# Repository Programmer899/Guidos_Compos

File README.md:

# Guidos_Compos
### - What is this project
My idea for this project is a little by the time I had left, meaning that it could not be too complex.
Therefore I ended up choosing a compass because I were interested in knowing how the magnetometer works.

### - What purpose does it have
We all know that you do not want to get stuck somewhere with a map but lost the compass along the way.
Therefore I have made this simple compass that simply points to north.

In addition to be a helping hand when reading the map, it is a sort of project that gives you perspective and learn stuff along the way.
Some of this is done in educational purpose.

### - Description:
It is a simple compas using a MMC5983MA-Magnetometer to detirmine the direction of the earth's magnetic field.
To read the values my "Guidos Compos" is using a bare minimum "ATtiny45-20SU SO-8" as it's cpu.
As for the power source, I am inputing power from a 3.7V 500mAh battery that is beeing lowered down to 3.3V for the "ATtiny" and the "Magnetometer". The leds are then powered directly from the battery and beeing controlled by the Attiny.
At some places there are also some capacitors placed out to take in fact of the small noise in the power, which can be an outcome from the battery. What the meaning of the capacitor is to balance out the noice giving you: noise -> mostly clear.

### - Problems along the way:
I have had a few problems along the way, as an example the wiring. I had to redo the entire wiring after noticing that my led lights were rotated incorrectly.
I have also had a little to much going on during this PCB week on [Half Life](https://halflife.hackclub.com/) meaning that I have not had much time to work on my project.
Though, in the end I got something to hopefully work.
### - Firmware:
[Firmware - Built](https://github.com/Programmer899/Guidos_Compos/blob/main/firmware.hex)
---
## Schematic:

## PCB

## 3D View

### Build Of Materials
**#** | **Item**                 | **Qty** | **Supplier** | **Cost/item** | **Total Cost** | **link**                                                                                                                     
-------|--------------------------|---------|--------------|---------------|----------------|------------------------------------------------------------------------------------------------------------------------------
 **1** | Voltage Regulator 3\.3V  | 1       | Electrokit   | $0\.13        | $0\.13         | https://www\.electrokit\.com/en/l7833\-sot\-223\-voltage\-regulator\-3\.3v\-1a                                               
 **2** | Attiny45                 | 1       | Electrokit   | $2\.90        | $2\.90         | https://www\.electrokit\.com/en/attiny45\-20su\-so\-8\-8\-bit\-mcu\-flash\-4k                                                
 **3** | Battery charger          | 1       | Electrokit   | $5\.50        | $5\.50         | https://www\.electrokit\.com/en/tp4056\-batteriladdare\-lipo\-microusb                                                       
 **4** | SK6812\-E                | 25      | Amazon       | $0\.04        | $1\.00         | https://www\.amazon\.se/gp/product/B0GGJFR5QX/ref=sw\_img\_1?smid=A2WIE6SW95T3HY&psc=1                                       
 **5** | Battery                  | 1       | Conrad       | $8\.90        | $8\.90         | https://www\.conrad\.se/sv/p/amewi\-rc\-batteripack\-lipo\-3\-7\-v\-500\-mah\-antal\-celler\-1\-softcase\-jst\-3436344\.html 
 **6** | MMC5983MA                | 1       | Digikey      | $3\.32        | $3\.32         | https://www\.digikey\.com/en/products/detail/memsic\-inc/MMC5983MA/10452795                                                  
 **TOTAL** | Estimated total shipping |         |              |               | $8\.23         |
 
 **NOTE:**
 The shipping is not fully accurate due to me having insuffisient time for the project - Time = money.  
 Meaning that the **shipping** is for Electrokit and Amazon. Conrad and Digikey are outside the money-range.

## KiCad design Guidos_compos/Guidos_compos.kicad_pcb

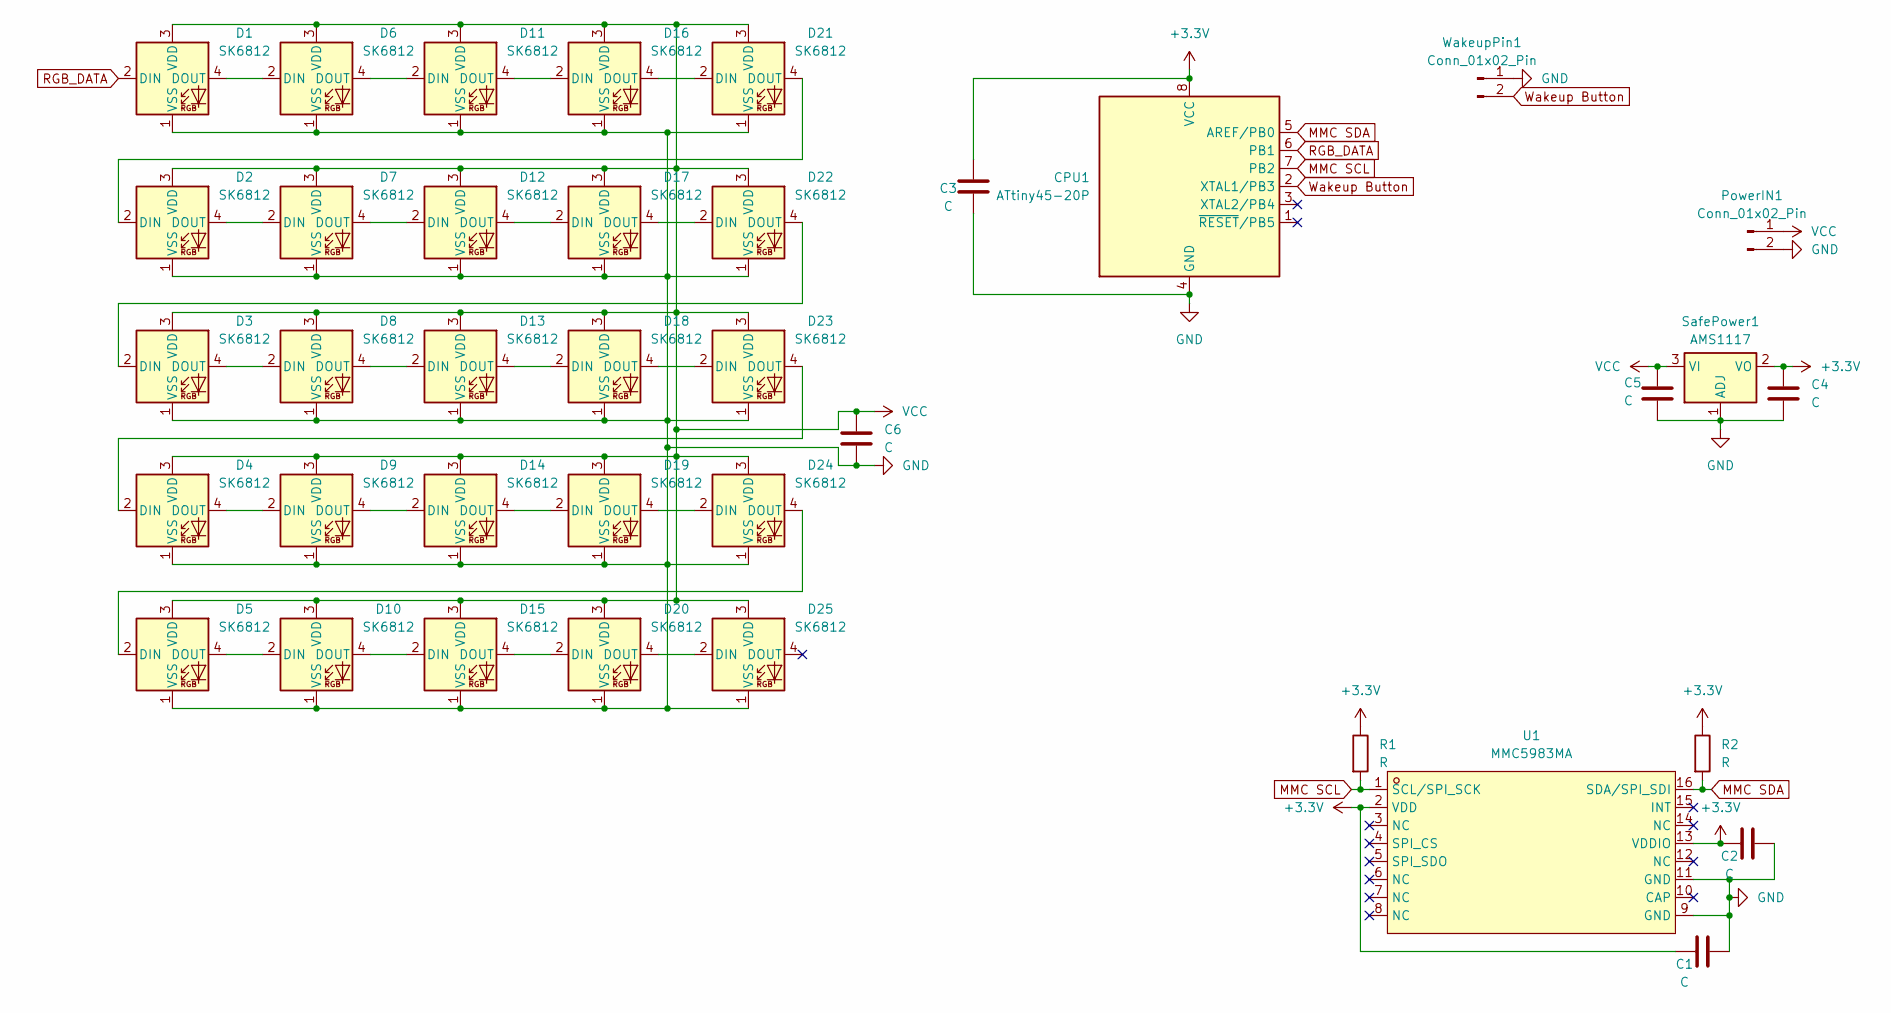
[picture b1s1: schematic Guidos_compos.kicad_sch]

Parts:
C1, C2, C3, C4, C5, C6: C; PinHeader_1x02_P1.00mm_Vertical
CPU1: ATtiny45-20P; DIP-8_W7.62mm
D1, D2, D3, D4, D5, D6, D7, D8, D9, D10, D11, D12, D13, D14, D15, D16, D17, D18, D19, D20, D21, D22, D23, D24, D25: SK6812; LED_SK6812_PLCC4_5.0x5.0mm_P3.2mm
PowerIN1: Conn_01x02_Pin; PinHeader_1x02_P1.00mm_Vertical
R1, R2: R; PinHeader_1x02_P1.00mm_Vertical
SafePower1: AMS1117; SOT-223-3_TabPin2
U1: MMC5983MA; MPN MMC5983MA; LCSC Part C404329
WakeupPin1: Conn_01x02_Pin; PinHeader_1x02_P1.00mm_Vertical

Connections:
+3.3V: C1.2, C2.2, C3.2, C4.1, CPU1.8 (VCC), R1.1, R2.1, SafePower1.2 (VO), U1.2 (VDD), U1.13 (VDDIO)
GND: C1.1, C2.1, C3.1, C4.2, C5.2, C6.2, CPU1.4 (GND), D1.1 (VSS), D2.1 (VSS), D3.1 (VSS), D4.1 (VSS), D5.1 (VSS), D6.1 (VSS), D7.1 (VSS), D8.1 (VSS), D9.1 (VSS), D10.1 (VSS), D11.1 (VSS), D12.1 (VSS), D13.1 (VSS), D14.1 (VSS), D15.1 (VSS), D16.1 (VSS), D17.1 (VSS), D18.1 (VSS), D19.1 (VSS), D20.1 (VSS), D21.1 (VSS), D22.1 (VSS), D23.1 (VSS), D24.1 (VSS), D25.1 (VSS), PowerIN1.2, SafePower1.1 (ADJ), U1.9 (GND), U1.11 (GND), WakeupPin1.1
MMC SCL: CPU1.7 (PB2), R1.2, U1.1 (SCL/SPI_SCK)
MMC SDA: CPU1.5 (AREF/PB0), R2.2, U1.16 (SDA/SPI_SDI)
unnamed: D1.4 (DOUT), D6.2 (DIN)
unnamed: D2.2 (DIN), D21.4 (DOUT)
unnamed: D2.4 (DOUT), D7.2 (DIN)
unnamed: D3.4 (DOUT), D8.2 (DIN)
unnamed: D4.4 (DOUT), D9.2 (DIN)
unnamed: D5.4 (DOUT), D10.2 (DIN)
unnamed: D10.4 (DOUT), D15.2 (DIN)
unnamed: D6.4 (DOUT), D11.2 (DIN)
unnamed: D11.4 (DOUT), D16.2 (DIN)
unnamed: D7.4 (DOUT), D12.2 (DIN)
unnamed: D12.4 (DOUT), D17.2 (DIN)
unnamed: D8.4 (DOUT), D13.2 (DIN)
unnamed: D13.4 (DOUT), D18.2 (DIN)
unnamed: D9.4 (DOUT), D14.2 (DIN)
unnamed: D14.4 (DOUT), D19.2 (DIN)
unnamed: D15.4 (DOUT), D20.2 (DIN)
unnamed: D16.4 (DOUT), D21.2 (DIN)
unnamed: D17.4 (DOUT), D22.2 (DIN)
unnamed: D18.4 (DOUT), D23.2 (DIN)
unnamed: D19.4 (DOUT), D24.2 (DIN)
unnamed: D20.4 (DOUT), D25.2 (DIN)
unnamed: D3.2 (DIN), D22.4 (DOUT)
unnamed: D4.2 (DIN), D23.4 (DOUT)
unnamed: D5.2 (DIN), D24.4 (DOUT)
RGB_DATA: CPU1.6 (PB1), D1.2 (DIN)
VCC: C5.1, C6.1, D1.3 (VDD), D2.3 (VDD), D3.3 (VDD), D4.3 (VDD), D5.3 (VDD), D6.3 (VDD), D7.3 (VDD), D8.3 (VDD), D9.3 (VDD), D10.3 (VDD), D11.3 (VDD), D12.3 (VDD), D13.3 (VDD), D14.3 (VDD), D15.3 (VDD), D16.3 (VDD), D17.3 (VDD), D18.3 (VDD), D19.3 (VDD), D20.3 (VDD), D21.3 (VDD), D22.3 (VDD), D23.3 (VDD), D24.3 (VDD), D25.3 (VDD), PowerIN1.1, SafePower1.3 (VI)
Wakeup Button: CPU1.2 (XTAL1/PB3), WakeupPin1.2

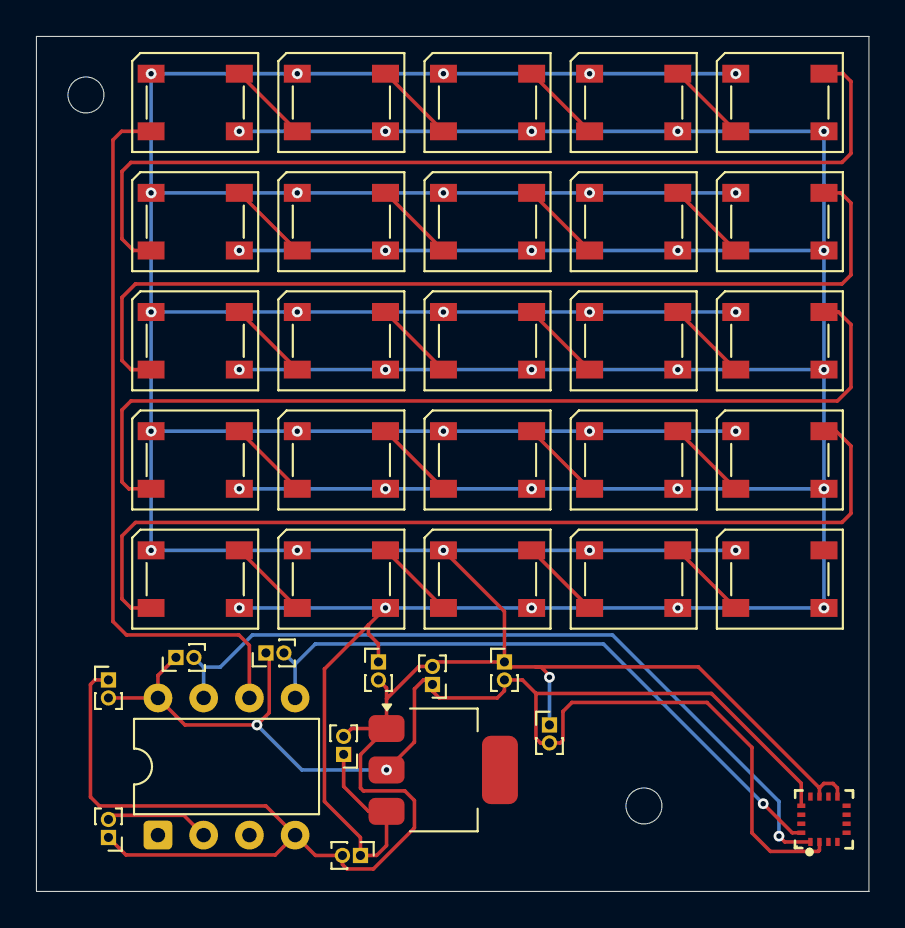
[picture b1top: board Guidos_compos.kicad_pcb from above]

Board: 2 copper layers, 46.2 x 47.5 mm, 38 parts (0 on the bottom side), 31 nets.
